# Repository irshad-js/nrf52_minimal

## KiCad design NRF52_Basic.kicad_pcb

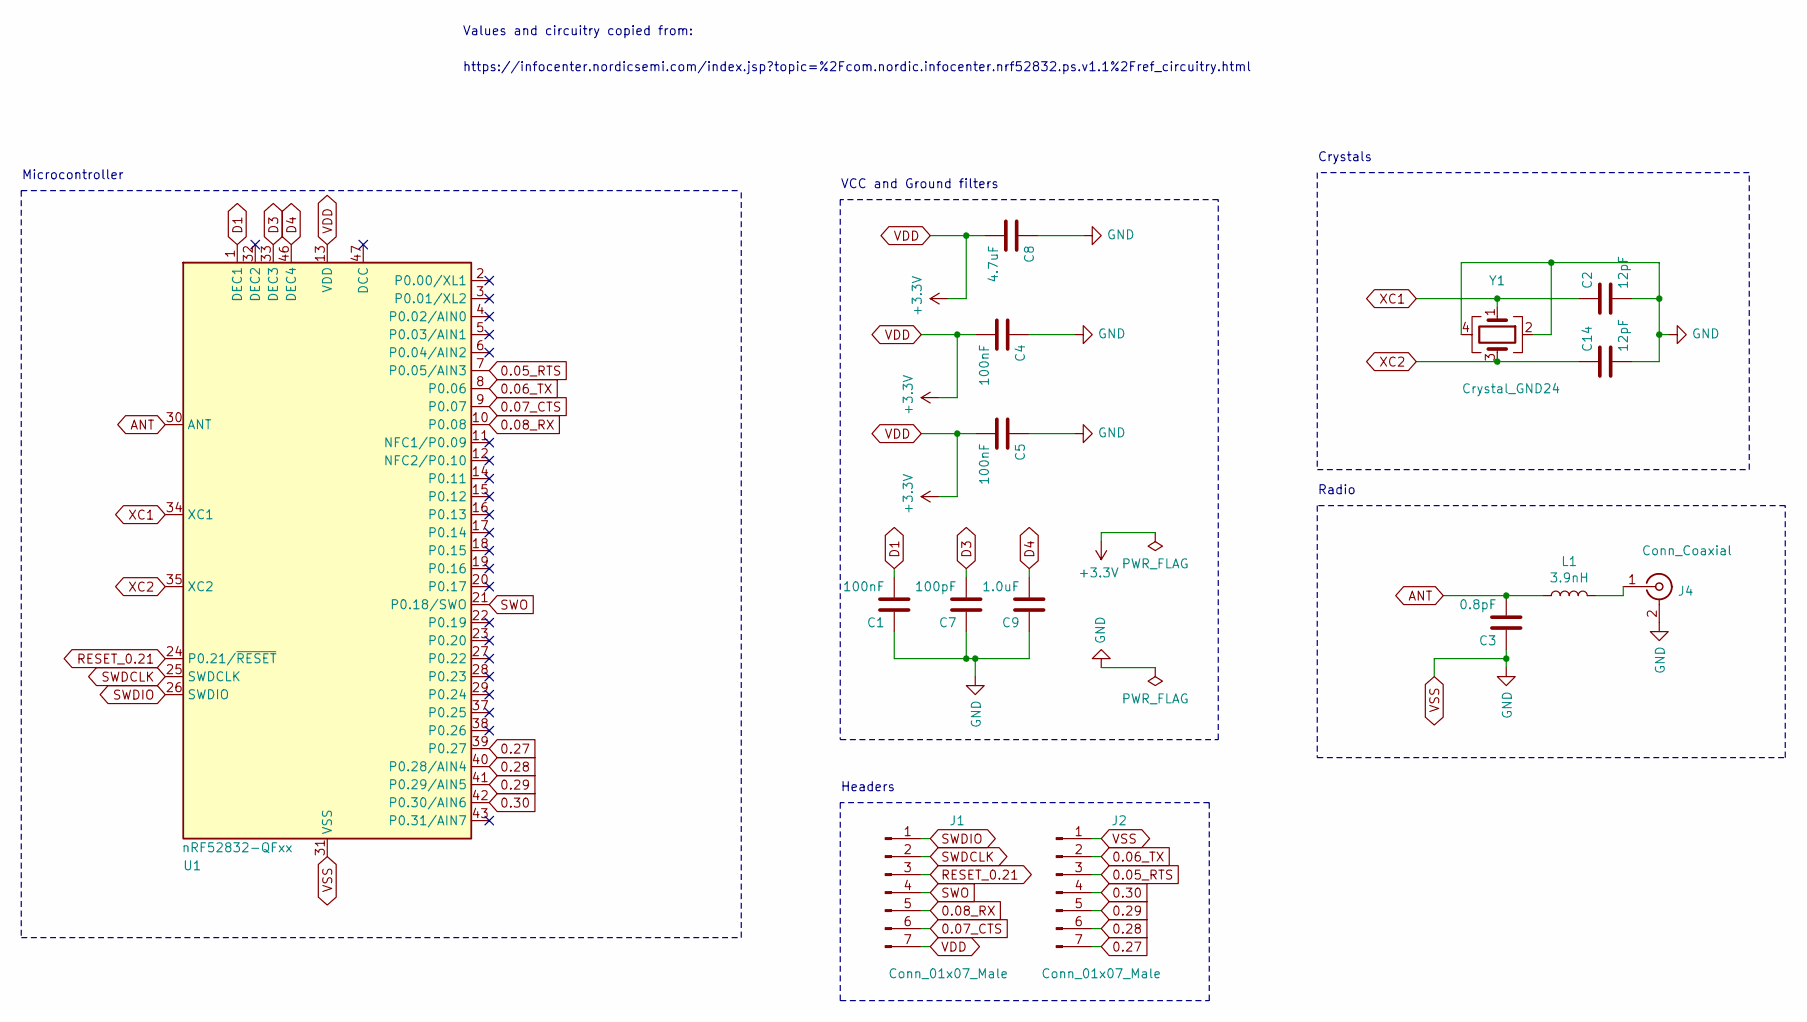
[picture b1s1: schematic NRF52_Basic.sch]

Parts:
C1, C4, C5: 100nF; C_0402_1005Metric; LCSC Part # C1525
C2, C14: 12pF; C_0402_1005Metric; LCSC Part # C1547
C3: 0.8pF; C_0402_1005Metric; LCSC Part # C285068
C7: 100pF; C_0402_1005Metric; LCSC Part # C1546
C8: 4.7uF; C_0603_1608Metric; LCSC Part # C19666
C9: 1.0uF; C_0603_1608Metric; LCSC Part # C15849
J1, J2: Conn_01x07_Male; PinSocket_1x07_P2.54mm_Vertical
J4: Conn_Coaxial; SMA_Samtec_SMA-J-P-H-ST-EM1_EdgeMount
L1: 3.9nH; L_0402_1005Metric; LCSC Part # C14033
U1: nRF52832-QFxx; QFN-48-1EP_6x6mm_P0.4mm_EP4.6x4.6mm; LCSC Part # C77540
Y1: Crystal_GND24; Crystal_SMD_3225-4Pin_3.2x2.5mm; LCSC Part # C91742

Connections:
0.05_RTS: J2.3, U1.7 (P0.05/AIN3)
0.06_TX: J2.2, U1.8 (P0.06)
0.07_CTS: J1.6, U1.9 (P0.07)
0.08_RX: J1.5, U1.10 (P0.08)
0.27: J2.7, U1.39 (P0.27)
0.28: J2.6, U1.40 (P0.28/AIN4)
0.29: J2.5, U1.41 (P0.29/AIN5)
0.30: J2.4, U1.42 (P0.30/AIN6)
ANT: C3.2, L1.1, U1.30 (ANT)
D1: C1.2, U1.1 (DEC1)
D3: C7.2, U1.33 (DEC3)
D4: C9.2, U1.46 (DEC4)
unnamed: J4.1 (In), L1.2
RESET_0.21: J1.3, U1.24 (P0.21/~RESET)
SWDCLK: J1.2, U1.25 (SWDCLK)
SWDIO: J1.1, U1.26 (SWDIO)
SWO: J1.4, U1.21 (P0.18/SWO)
VDD: C4.2, C5.2, C8.2, J1.7, U1.13 (VDD), U1.36 (VDD), U1.48 (VDD)
VSS: C1.1, C2.2, C3.1, C4.1, C5.1, C7.1, C8.1, C9.1, C14.2, J2.1, J4.2 (Ext), U1.31 (VSS), U1.45 (VSS), U1.49 (VSS), Y1.2, Y1.4
XC1: C2.1, U1.34 (XC1), Y1.1
XC2: C14.1, U1.35 (XC2), Y1.3

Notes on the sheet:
Microcontroller
VCC and Ground filters
Crystals
Radio
Headers
https://infocenter.nordicsemi.com/index.jsp?topic=%2Fcom.nordic.infocenter.nrf52832.ps.v1.1%2Fref_circuitry.html
Values and circuitry copied from:

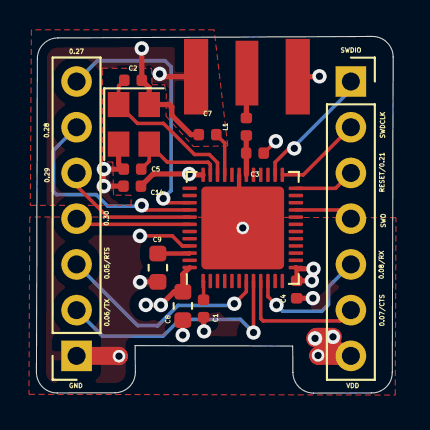
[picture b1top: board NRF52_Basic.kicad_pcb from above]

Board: 4 copper layers, 19.8 x 19.8 mm, 15 parts (0 on the bottom side), 21 nets.

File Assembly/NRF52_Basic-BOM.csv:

Comment,Designator,Footprint,LCSC
"100nF","C1,C4,C5","Capacitor_SMD:C_0402_1005Metric",""
"12pF","C2,C14","Capacitor_SMD:C_0402_1005Metric",""
"0.8pF","C3","Capacitor_SMD:C_0402_1005Metric",""
"100pF","C7","Capacitor_SMD:C_0402_1005Metric",""
"4.7uF","C8","Capacitor_SMD:C_0603_1608Metric",""
"1.0uF","C9","Capacitor_SMD:C_0603_1608Metric",""
"Conn_01x07_Male","J1,J2","Connector_PinSocket_2.54mm:PinSocket_1x07_P2.54mm_Vertical",""
"Conn_Coaxial","J4","Connector_Coaxial:SMA_Samtec_SMA-J-P-H-ST-EM1_EdgeMount",""
"3.9nH","L1","Inductor_SMD:L_0402_1005Metric",""
"nRF52832-QFxx","U1","Package_DFN_QFN:QFN-48-1EP_6x6mm_P0.4mm_EP4.6x4.6mm",""
"Crystal_GND24","Y1","Crystal:Crystal_SMD_3225-4Pin_3.2x2.5mm",""

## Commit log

2021-02-14 First good design commit
2021-02-20 Improved ground fills and structure
2021-03-01 Intermediate mods
2021-03-01 Intermediate mods -2
2021-03-01 Optimized the layers and component fixtures
2022-05-02 intermediate
